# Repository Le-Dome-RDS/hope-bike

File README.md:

# hope-bike
An open source Pedalling Assistant Sytem for 26" wheeled bikes 

Licence : CC-BY-SA

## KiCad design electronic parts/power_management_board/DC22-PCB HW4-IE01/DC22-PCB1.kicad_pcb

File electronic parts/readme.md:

#Electronic parts

This folder contains datasheet, eagle project and schematic for the three different PCB files : 

* the button card that contains the three buttons used for the control of the speed by the user,
* the command card that contains LEDs used to visualize both the battery level and the speed assist level. It also contains the arduino board.
*  the power management card that contains all the power electronic stuff necessary to drive the brushless motor using the electrical power battery.

The datasheets for the electronical devices used in the cards and the commercial items required for the kit (battery, motor and the pedal sensor) are also avalaible

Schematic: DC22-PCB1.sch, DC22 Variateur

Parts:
C1, C27: 220µF 50V
C2, C5, C6, C7, C9, C10, C11, C12, C13, C14, C18, C19, C20, C28: 10µF 50V
C3, C8: 10nF
C4: 680µF 16V
C15, C16, C17, C21, C22, C23, C24, C25, C26, C29, C30, C31: 1nF
D1: 12V
D2: DIODESCH
D3, D4, D5, D6, D7: DIODE
L1: 100µH
P1: CONN_8
P2: CONN_12
P3, P4: CONN_5
Q1, Q2, Q3, Q4, Q5, Q6: MOSFET_N
R1, R6: 2,2K
R2, R14, R15, R16, R17, R18, R19, R22: 1K
R3: 82k
R4, R20: 56K
R5: 10K
R7, R21, R23, R24: 100E
R8, R9, R10, R11, R12, R13: 100
R25, R26, R27: 4,7K
U1: LM2576
U2: 78L05
U3: ASC712
U4: LM7812
U5: PIC12F1822
U6: PIC16F1509
U7, U8, U9: IRS21850
U10, U11: IR4427
W1, W2, W3, W4: TEST
X1: 16MHz

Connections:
+5V Hall: C6.1, C8.1, C10.1, C11.1, P2.8, P3.2, P4.2, R4.1, R6.1, R17.1, R18.1, R19.1, R20.1, R22.2, R23.2, U3.8 (Vcc), U5.1 (Vdd), U6.1 (Vdd), W4.2
+12V: C12.1, C13.1, C14.1, C28.1, D4.1 (A), D5.1 (A), D6.1 (A), U4.VO, U7.1 (Vcc), U8.1 (Vcc), U9.1 (Vcc), U10.6 (Vcc), U11.6 (Vcc)
+36V: Q1.D, Q3.D, Q5.D, R25.1, R26.1, R27.1, U3.1 (IP+), U3.2 (IP+)
+36V In Inter: C1.1, D1.2, P1.2, R3.1, U1.1 (Vin)
+36V Out Inter: C27.1, P1.1, P2.1, U3.3 (IP-), U3.4 (IP-)
+V Bus: C4.1, L1.2, P1.3, R1.2, U2.VI
A: C20.2, P2.3, Q1.S, Q2.D, R25.2, U9.6 (Vs)
B: C19.2, P2.4, Q3.S, Q4.D, R26.2, U8.6 (Vs)
BIONet: C30.2, D3.1 (A), D7.1 (A), P1.4, R6.2, R7.1, R21.1
C: C18.2, P2.5, P2.6, Q5.S, Q6.D, R27.2, U7.6 (Vs)
GND Bus: C1.2, C2.2, C3.2, C4.2, C5.2, C6.2, C7.2, C8.2, C9.2, C10.2, C11.2, C12.2, C13.2, C14.2, C15.2, C16.2, C17.2, C21.1, C22.1, C23.1, C24.2, C25.1, C26.2, C27.2, C28.2, C29.2, C30.1, C31.2, D2.1 (A), P1.5, P1.8, P2.2, P2.7, P2.12, P3.3, P4.3, Q2.S, Q4.S, Q6.S, R5.2, U1.3 (GND), U1.5 (On/OFF), U2.GND, U3.5 (GND), U4.GND, U5.8 (Vss), U6.20 (Vss), U7.4 (GND), U8.4 (GND), U9.4 (GND), U10.2 (InA), U10.3 (GND), U11.3 (GND)
Hall A: C21.2, R14.1, U6.11 (RB6), W3.2
Hall B: C22.2, R15.1, U6.16 (RC0)
Hall C: C23.2, R16.1, U6.17 (RA2)
Hall Motor A: P2.9, R14.2, R17.2
Hall Motor B: P2.10, R15.2, R18.2
Hall Motor C: P2.11, R16.2, R19.2
HighA: Q1.G, U9.7 (Out)
HighB: Q3.G, U8.7 (Out)
HighC: Q5.G, U7.7 (Out)
HighSide A: R10.1, U6.5 (RC5)
HighSide B: R9.1, U6.7 (RC3)
HighSide C: R8.1, U6.15 (RC1)
Imot: C7.1, R2.2, U5.5 (RA2)
LowA: Q2.G, U10.5 (OutB)
LowB: Q4.G, U11.7 (OutA)
LowC: Q6.G, U11.5 (OutB)
LowSide A: R11.1, U6.6 (RC4)
LowSide B: R12.1, U6.14 (RC2)
LowSide C: R13.1, U6.13 (RB4)
unnamed: P4.4, U6.19 (RA0/ICSPDAT)
unnamed: P4.5, U6.18 (RA1/ICSPCLK)
unnamed: R2.1, U3.7 (Out)
unnamed: D7.2 (K), U5.3 (RA4)
unnamed: C25.2, R12.2, U11.2 (InA)
unnamed: C26.1, R13.2, U11.4 (InB)
unnamed: R22.1, R24.2, W1.2
unnamed: C5.1, U2.VO, W4.1
unnamed: C29.1, P1.6, R23.1
unnamed: P3.1, R20.2, U5.4 (RA3/Vpp/MCLR), W1.1
unnamed: P3.5, U5.6 (RA1/ICSPCLK), W3.1
unnamed: P3.4, U5.7 (RA0/ICSPDAT), W2.1
unnamed: R21.2, U5.2 (RA5)
unnamed: D2.2 (K), L1.1, U1.2 (Out)
unnamed: R1.1, U1.4 (FeedBack)
unnamed: P4.1, R4.2, U6.4 (RA3/Vpp/MCLR)
unnamed: U6.2 (RA5), X1.2
unnamed: D3.2 (K), U6.10 (RB7)
unnamed: R7.2, U6.12 (RB5)
unnamed: C24.1, R11.2, U10.4 (InB)
unnamed: C17.1, R10.2, U9.2 (In)
unnamed: C20.1, D6.2 (K), U9.8 (Vboot)
unnamed: C3.1, U3.6 (Filt)
unnamed: U6.3 (RA4), X1.1
unnamed: C2.1, D1.1, U4.VI
unnamed: C15.1, R8.2, U7.2 (In)
unnamed: C18.1, D4.2 (K), U7.8 (Vboot)
unnamed: C19.1, D5.2 (K), U8.8 (Vboot)
unnamed: C16.1, R9.2, U8.2 (In)
Pedalage: C31.1, P1.7, R24.1
Vbatt: C9.1, R3.2, R5.1, W2.2

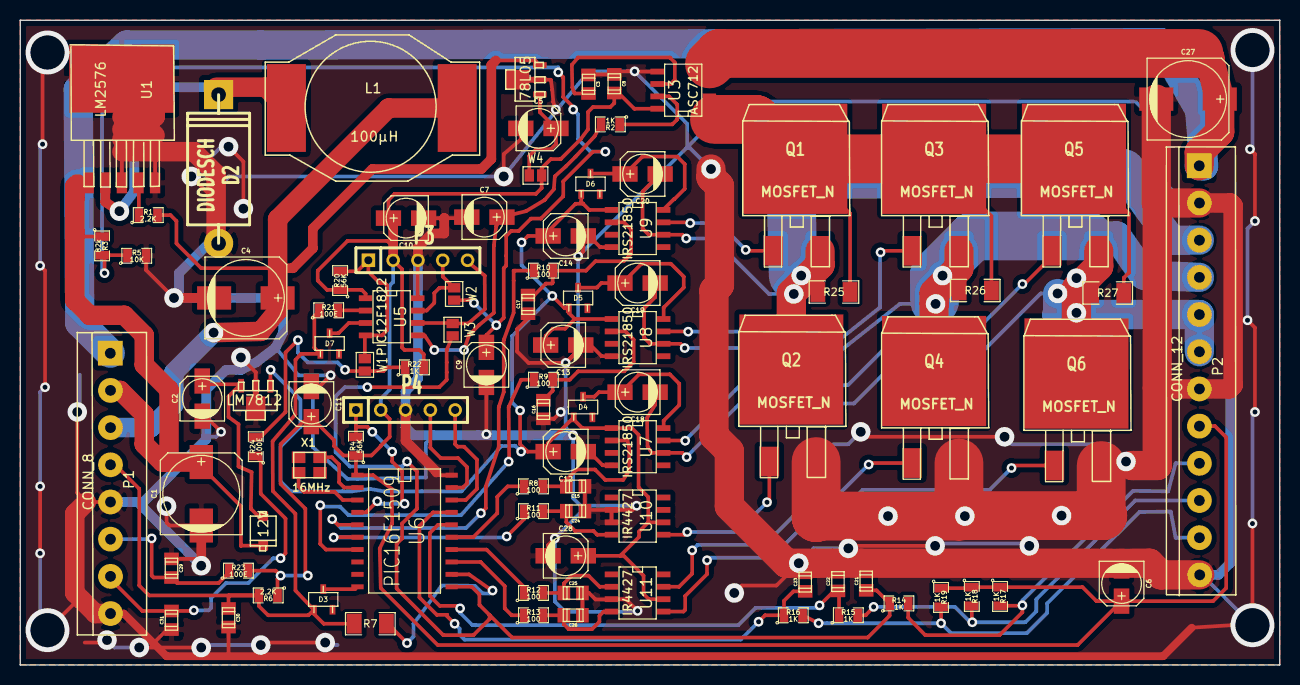
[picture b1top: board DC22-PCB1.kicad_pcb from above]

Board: 2 copper layers, 129.0 x 66.0 mm, 92 parts (0 on the bottom side), 61 nets.

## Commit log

2016-10-20 First commit with JMR
    Data sheet and other documentations
2016-10-20 add read me to electronic
2016-10-20 test by JMR
    To be deleted
2017-01-19 adding folder structure and read-me files
    To start with the 18th of January work session.
2017-01-19 source code for the command card and the power management card
2017-01-19 readme.md updates
    Update of few readme.md
2017-01-19 pdf...
    pdf files for the schematic and the pcb of the different electronic card
2017-01-19 documents maj
    Modification in Readme, odt files of the doc
2017-01-19 update docs
2017-01-19 BOM renaming
2017-01-19 BOM fastenings
2017-02-24 - New code for the command card based on the work of Gaylord Lebrun and Medhi Brinis. - a report (in french) is provided in the documents section that explains how the command works.
2017-02-24 - correction in the DC00_architecture document
2017-02-24 Remove of .webloc (apple only) and description of web link in the readme.md files.
2017-03-15 documentation update
    Mainly document update to programm the boards
2017-03-15 Mise à jour code carte commande
    Mise à jour de la machine d'état pour une gestion plus fine des
    dépassements du courant MAX
2017-03-17 Documentation update
    User manuel
    diy manual
    certificate
2017-03-17 Last update before DIY workshop
    Doc updates
2020-01-31 HnB hardware version 2 directory creation for command card programming
2020-01-31 Readme.md update
2020-01-31 cleanup for stating software command for v2 hardware
2020-02-03 test
2020-02-03 Ajout des variables globales
2020-02-03 rename filename and starts heltec32 integration
2020-02-24 Integration of the command lines for the v2 electronic device
2020-02-24 nightly updates
2020-02-26 after two days working on the code
2020-03-02 still one bug to solve
2020-03-10 version après premier atelier montage au dôme
2020-07-23 vecy close to the final version before going in holidays
2021-03-03 2021 update : new state to slow down quietly the motor, button update
2021-03-04 2021 03 04 update : median filter for the measurements of the bike speed
2021-03-22 2021 03 22 : motor stop detection. Modulation of the deltaPWM with the current
2021-03-24 2021 03 25 : better motor stop detection and more precise PWM moduluation ; screen ajustement ; special keyboard option update
2021-04-13 version 1.99. La version 2.0 est presque, mais alors presque, terminée. Et Yohoho et une bouteille de rhum.
2021-04-14 integration des plans openscad
2021-04-15 integration des plans pour le capteur de hall de la roue
2021-04-15 Optimisation des boitiers
2021-04-15 Optimisation des boitiers, suite
